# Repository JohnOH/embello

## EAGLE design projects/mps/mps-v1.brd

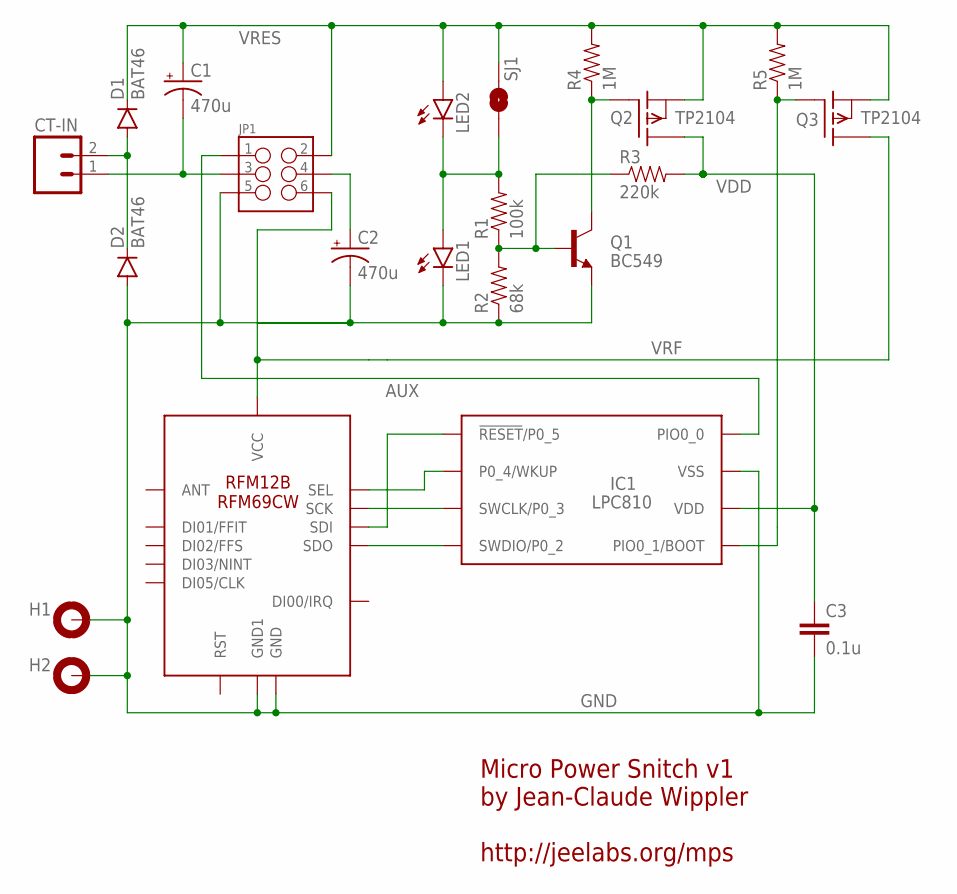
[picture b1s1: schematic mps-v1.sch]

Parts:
C1, C2: 470u; CPOL-RADIAL-100UF-25V
C3: 0.1u; CAP-PTH-SMALL
CT-IN: M023.5MM; SCREWTERMINAL-3.5MM-2
D1, D2: BAT46; DIODE-1N4148
H1, H2: MOUNT-PAD-ROUND2.8; 2,8-PAD
IC1: LPC810; DIP8
JP1: M03X2NO_SILK; 2X3-NS
LED1, LED2: LED3MM
Q1: BC549; TO92
Q2, Q3: TP2104; TO92
R1: 100k; AXIAL-0.3
R2: 68k; AXIAL-0.3
R3: 220k; AXIAL-0.3
R4, R5: 1M; AXIAL-0.3
RFM12B/69CW: RFM12B/69CW
SJ1: JUMPER-PAD-2-NO; PAD-JUMPER-2-NO_NO_SILK

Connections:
AUX: IC1.P$8 (PIO0_0), JP1.1
GND: C2.2 (-), C3.2, D2.A, H1.B2,8, H2.B2,8, IC1.P$7 (VSS), JP1.5, LED1.K (C), Q1.1 (E), R2.P$1 (1), RFM12B/69CW.GND, RFM12B/69CW.GND1
unnamed: CT-IN.2, D1.A, D2.C
unnamed: C2.1 (+), JP1.4
unnamed: IC1.P$3 (SWCLK/P0_3), RFM12B/69CW.SCK
unnamed: C1.2 (-), CT-IN.1, JP1.3
unnamed: LED1.A, LED2.K (C), R1.P$2 (2), SJ1.1
unnamed: Q1.3 (C), Q2.2 (G), R4.P$1 (1)
unnamed: Q1.2 (B), R1.P$1 (1), R2.P$2 (2), R3.P$1 (1)
unnamed: IC1.P$1 (!RESET!/P0_5), RFM12B/69CW.SDI
unnamed: IC1.P$2 (P0_4/WKUP), RFM12B/69CW.SEL
unnamed: IC1.P$4 (SWDIO/P0_2), RFM12B/69CW.SDO
unnamed: IC1.P$5 (PIO0_1/BOOT), Q3.2 (G), R5.P$1 (1)
VDD: C3.1, IC1.P$6 (VDD), Q2.3 (D), R3.P$2 (2)
VRES: C1.1 (+), D1.C, JP1.2, LED2.A, Q2.1 (S), Q3.1 (S), R4.P$2 (2), R5.P$2 (2), SJ1.2
VRF: JP1.6, Q3.3 (D), RFM12B/69CW.VDD (VCC)

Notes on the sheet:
Micro Power Snitch v1 by Jean-Claude Wippler http://jeelabs.org/mps

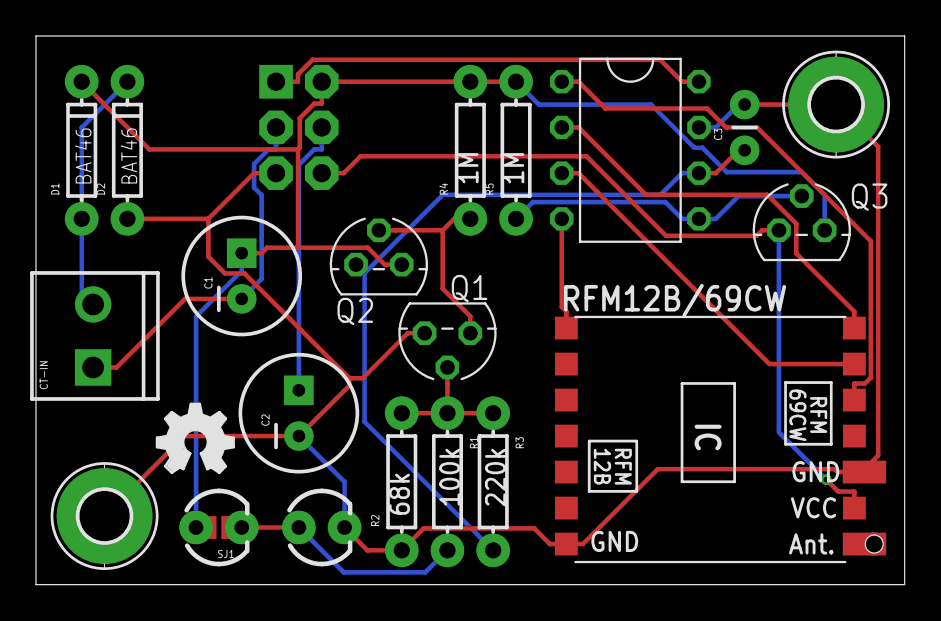
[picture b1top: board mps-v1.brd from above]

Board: 2 copper layers, 48.3 x 30.5 mm, 23 parts (0 on the bottom side), 16 nets.

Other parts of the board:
LOGO1: OSHW_LOGO_FILLX0150-NT; OSHW_FILLX150_NOTEXT

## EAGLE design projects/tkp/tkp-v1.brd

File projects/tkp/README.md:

# Tinker Pico

The "Tinker Pico" is a breakout board for the 32-bit LPC824 microcontroller.  
It includes a 5V -> 3.3V regulator and an FTDI-compatible header for uploading.

See <http://jeelabs.org/tkp> for details.

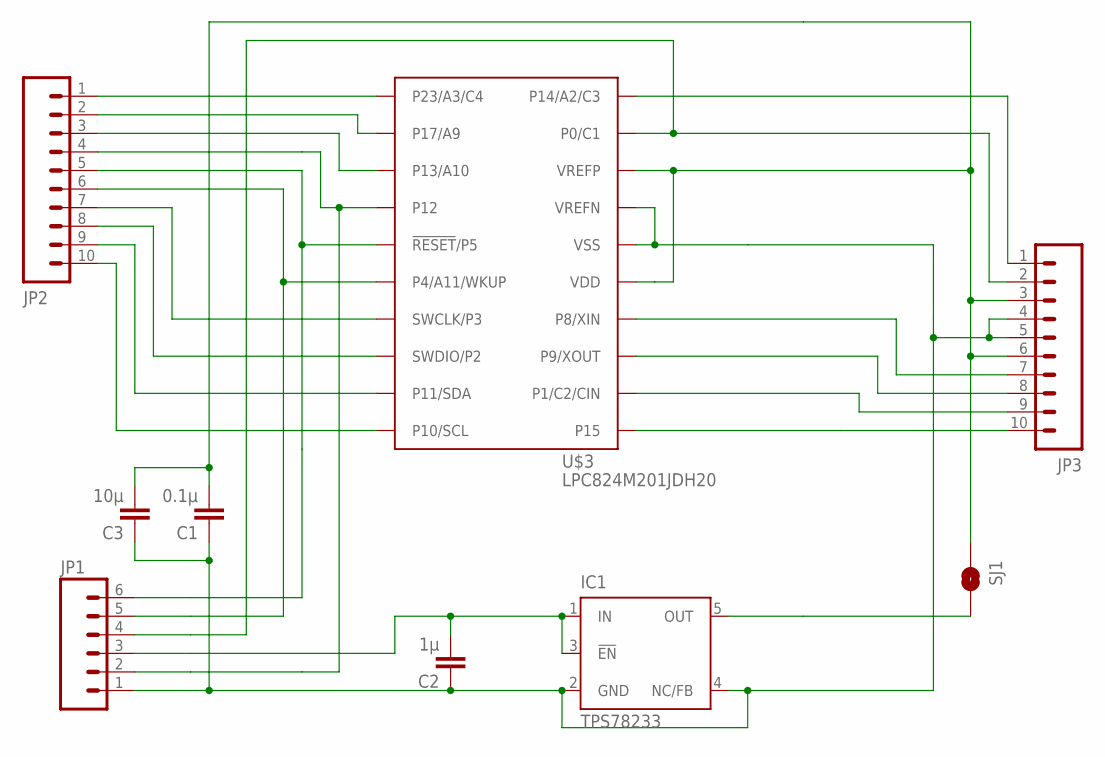
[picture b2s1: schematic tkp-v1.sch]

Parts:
C1: 0.1µ; C0603K
C2: 1µ; C0603K
C3: 10µ; C0805K
IC1: TPS78233; SOT23-DBV
JP1: M06LONGPADS; 1X06_LONGPADS
JP2, JP3: M10NO_SILK_PTH_FEMALE; 1X10_NO_SILK
SJ1: SOLDERJUMPERTRACE; SJ_2S-TRACE
U$3: LPC824M201JDH20; TSSOP20

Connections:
GND: C1.1, C2.1, C3.1, IC1.2 (GND), IC1.4 (NC/FB), JP1.1, JP3.4, JP3.5, U$3.16 (VSS), U$3.17 (VREFN)
unnamed: JP2.1, U$3.1 (P23/A3/C4)
unnamed: C2.2, IC1.1 (IN), IC1.3 (!EN), JP1.3
unnamed: JP1.4, JP3.2, U$3.19 (P0/C1)
unnamed: C1.2, C3.2, JP3.3, JP3.6, SJ1.1, U$3.15 (VDD), U$3.18 (VREFP)
unnamed: JP1.5, JP2.6, U$3.6 (P4/A11/WKUP)
unnamed: JP2.2, U$3.2 (P17/A9)
unnamed: JP3.1, U$3.20 (P14/A2/C3)
unnamed: JP3.7, U$3.14 (P8/XIN)
unnamed: JP3.8, U$3.13 (P9/XOUT)
unnamed: JP3.9, U$3.12 (P1/C2/CIN)
unnamed: JP3.10, U$3.11 (P15)
unnamed: JP1.2, JP2.4, U$3.4 (P12)
unnamed: JP2.3, U$3.3 (P13/A10)
unnamed: JP1.6, JP2.5, U$3.5 (!RESET!/P5)
unnamed: IC1.5 (OUT), SJ1.2
unnamed: JP2.7, U$3.7 (SWCLK/P3)
unnamed: JP2.8, U$3.8 (SWDIO/P2)
unnamed: JP2.9, U$3.9 (P11/SDA)
unnamed: JP2.10, U$3.10 (P10/SCL)

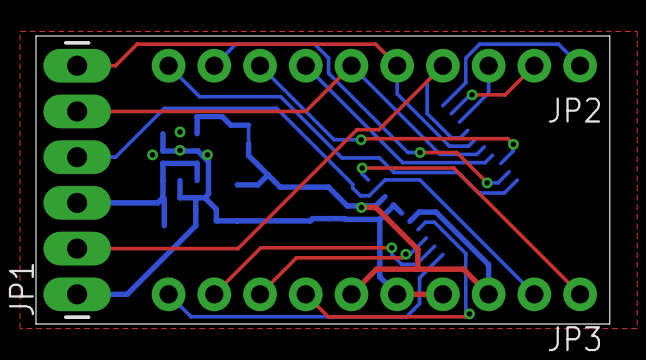
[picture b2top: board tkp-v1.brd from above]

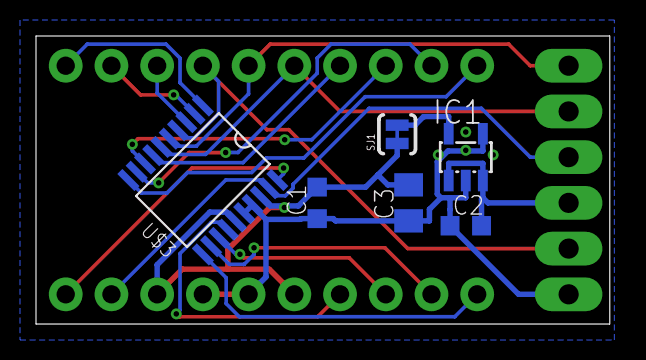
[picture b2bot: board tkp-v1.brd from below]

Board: 2 copper layers, 31.9 x 16.0 mm, 9 parts (6 on the bottom side), 20 nets.

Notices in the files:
parts and their libraries:
SparkFun-Capacitors: Licensing: Creative Commons ShareAlike 4.0 International - https://creativecommons.org/licenses/by-sa/4.0
